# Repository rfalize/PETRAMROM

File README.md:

# PETRAMROM
PET RAM/ROM Replacement

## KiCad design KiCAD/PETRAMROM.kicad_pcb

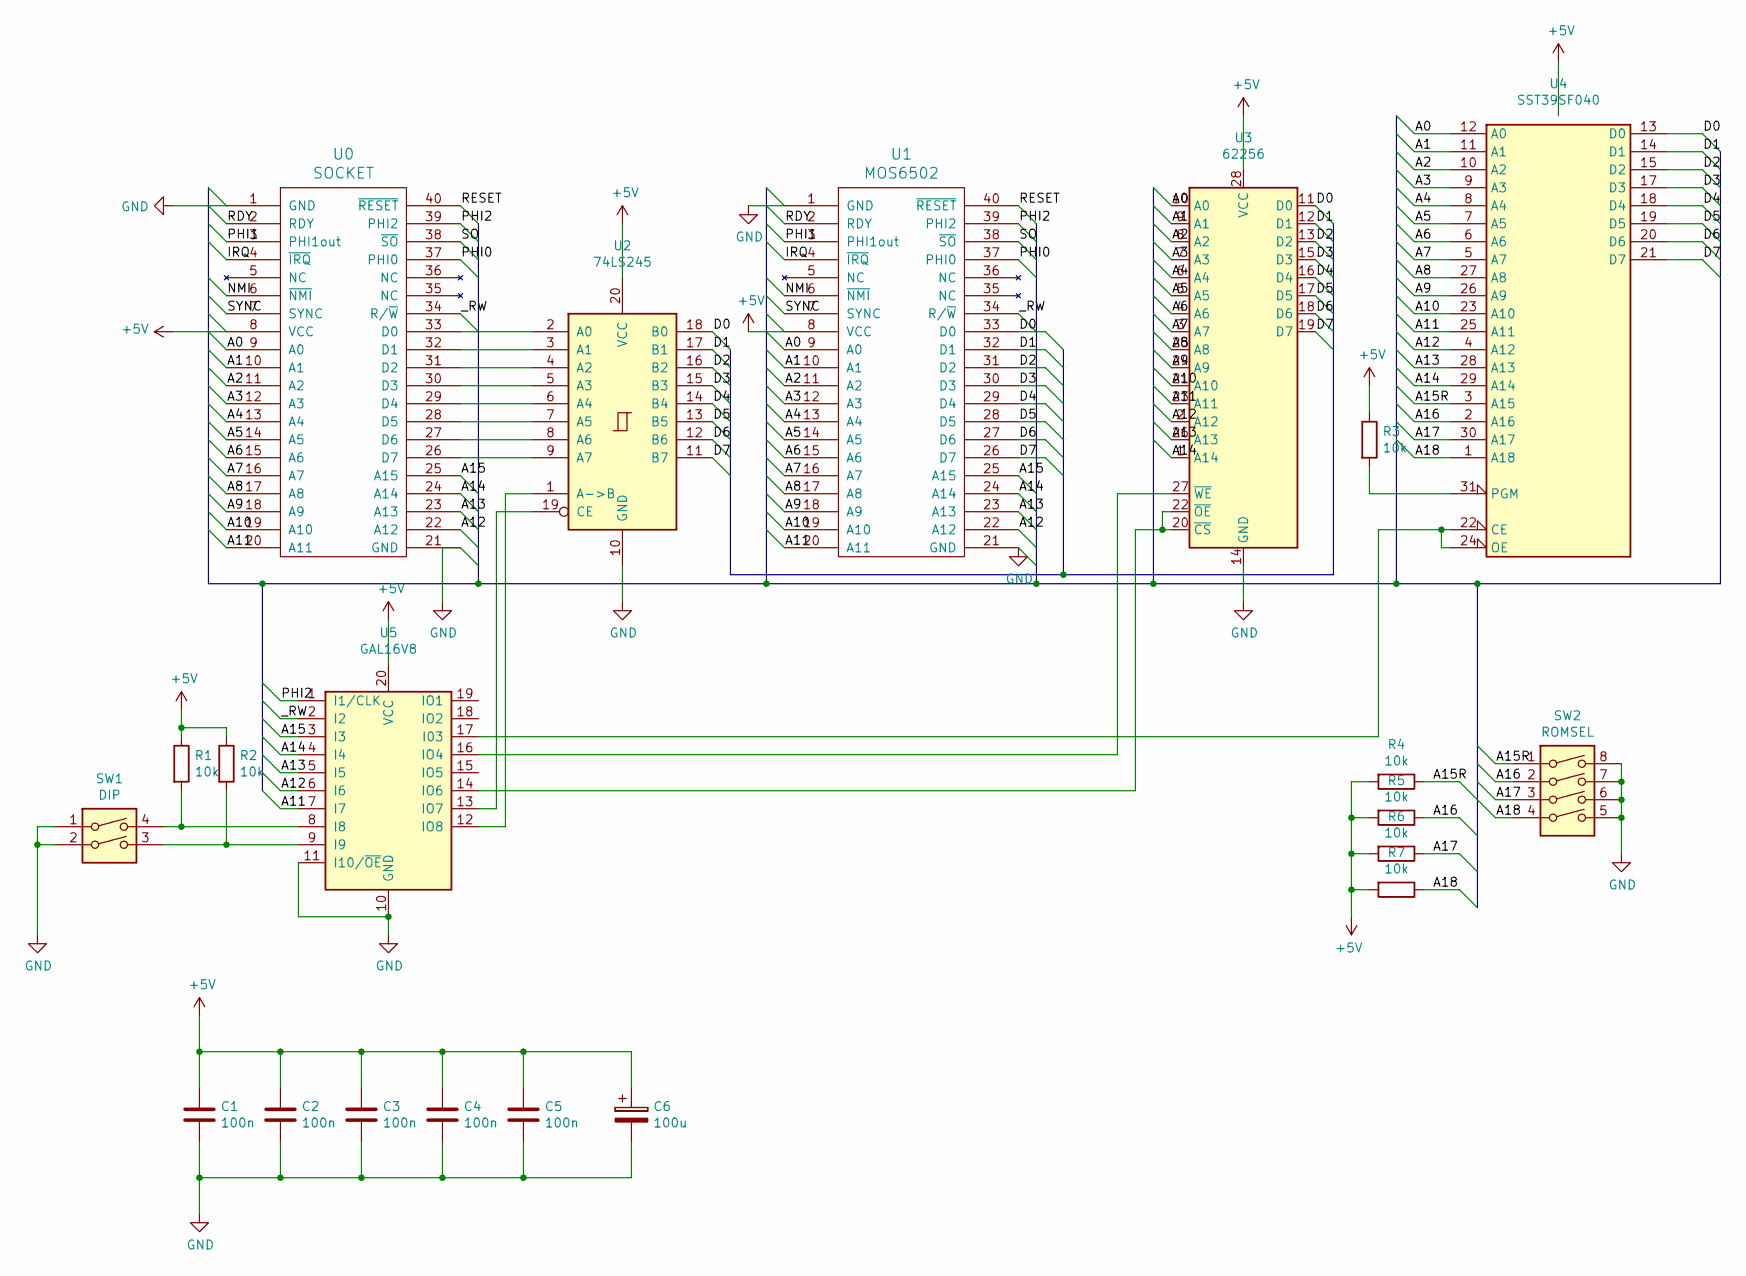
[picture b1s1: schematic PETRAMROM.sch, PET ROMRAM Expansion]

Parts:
C1, C2, C3, C4, C5: 100n; C_Disc_D5.0mm_W2.5mm_P5.00mm
C6: 100u; C_Radial_D6.3mm_H5.0mm_P2.50mm
R1, R2, R3, R4, R5, R6, R7: 10k; R_Axial_DIN0207_L6.3mm_D2.5mm_P2.54mm_Vertical
SW1: DIP; SW_DIP_SPSTx02_Slide_9.78x7.26mm_W7.62mm_P2.54mm
SW2: ROMSEL; SW_DIP_SPSTx04_Slide_9.78x12.34mm_W7.62mm_P2.54mm
U0: SOCKET; DIP-40_W15.24mm_Socket_LongPads
U1: MOS6502; DIP-40_W15.24mm_LongPads
U2: 74LS245; DIP-20_W7.62mm_LongPads
U3: 62256; DIP-28_W15.24mm_LongPads
U4: SST39SF040; DIP-32_W15.24mm_LongPads
U5: GAL16V8; DIP-20_W7.62mm_LongPads

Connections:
+5V: C1.1, C2.1, C3.1, C4.1, C5.1, C6.1, R1.1, R2.1, R3.1, R4.2, R5.2, R6.2, R7.2, U0.8 (VCC), U1.8 (VCC), U2.20 (VCC), U3.28 (VCC), U4.32 (VCC), U5.20 (VCC)
/A0: U0.9 (A0), U1.9 (A0), U3.10 (A0), U4.12 (A0)
/A1: U0.10 (A1), U1.10 (A1), U3.9 (A1), U4.11 (A1)
/A2: U0.11 (A2), U1.11 (A2), U3.8 (A2), U4.10 (A2)
/A3: U0.12 (A3), U1.12 (A3), U3.7 (A3), U4.9 (A3)
/A4: U0.13 (A4), U1.13 (A4), U3.6 (A4), U4.8 (A4)
/A5: U0.14 (A5), U1.14 (A5), U3.5 (A5), U4.7 (A5)
/A6: U0.15 (A6), U1.15 (A6), U3.4 (A6), U4.6 (A6)
/A7: U0.16 (A7), U1.16 (A7), U3.3 (A7), U4.5 (A7)
/A8: U0.17 (A8), U1.17 (A8), U3.25 (A8), U4.27 (A8)
/A9: U0.18 (A9), U1.18 (A9), U3.24 (A9), U4.26 (A9)
/A10: U0.19 (A10), U1.19 (A10), U3.21 (A10), U4.23 (A10)
/A11: U0.20 (A11), U1.20 (A11), U3.23 (A11), U4.25 (A11), U5.7 (I7)
/A12: U0.22 (A12), U1.22 (A12), U3.2 (A12), U4.4 (A12), U5.6 (I6)
/A13: U0.23 (A13), U1.23 (A13), U3.26 (A13), U4.28 (A13), U5.5 (I5)
/A14: U0.24 (A14), U1.24 (A14), U3.1 (A14), U4.29 (A14), U5.4 (I4)
/A15: U0.25 (A15), U1.25 (A15), U5.3 (I3)
/A15R: R4.1, SW2.1, U4.3 (A15)
/A16: R5.1, SW2.2, U4.2 (A16)
/A17: R6.1, SW2.3, U4.30 (A17)
/A18: R7.1, SW2.4, U4.1 (A18)
/D0: U1.33 (D0), U2.18 (B0), U3.11 (D0), U4.13 (D0)
/D1: U1.32 (D1), U2.17 (B1), U3.12 (D1), U4.14 (D1)
/D2: U1.31 (D2), U2.16 (B2), U3.13 (D2), U4.15 (D2)
/D3: U1.30 (D3), U2.15 (B3), U3.15 (D3), U4.17 (D3)
/D4: U1.29 (D4), U2.14 (B4), U3.16 (D4), U4.18 (D4)
/D5: U1.28 (D5), U2.13 (B5), U3.17 (D5), U4.19 (D5)
/D6: U1.27 (D6), U2.12 (B6), U3.18 (D6), U4.20 (D6)
/D7: U1.26 (D7), U2.11 (B7), U3.19 (D7), U4.21 (D7)
/IRQ: U0.4 (~IRQ), U1.4 (~IRQ)
/NMI: U0.6 (~NMI), U1.6 (~NMI)
/PHI0: U0.37 (PHI0), U1.37 (PHI0)
/PHI1: U0.3 (PHI1out), U1.3 (PHI1out)
/PHI2: U0.39 (PHI2), U1.39 (PHI2), U5.1 (I1/CLK)
/RDY: U0.2 (RDY), U1.2 (RDY)
/RESET: U0.40 (~RESET), U1.40 (~RESET)
/SO: U0.38 (~SO), U1.38 (~SO)
/SYNC: U0.7 (SYNC), U1.7 (SYNC)
/_RW: U0.34 (R/~W), U1.34 (R/~W), U5.2 (I2)
GND: C1.2, C2.2, C3.2, C4.2, C5.2, C6.2, SW1.1, SW1.2, SW2.5, SW2.6, SW2.7, SW2.8, U0.1 (GND), U0.21 (GND), U1.1 (GND), U1.21 (GND), U2.10 (GND), U3.14 (GND), U4.16 (GND), U5.10 (GND), U5.11 (I10/~OE~)
unnamed: R1.2, SW1.4, U5.8 (I8)
unnamed: R2.2, SW1.3, U5.9 (I9)
unnamed: R3.2, U4.31 (PGM)
unnamed: U0.26 (D7), U2.9 (A7)
unnamed: U0.27 (D6), U2.8 (A6)
unnamed: U0.28 (D5), U2.7 (A5)
unnamed: U0.29 (D4), U2.6 (A4)
unnamed: U0.30 (D3), U2.5 (A3)
unnamed: U0.31 (D2), U2.4 (A2)
unnamed: U0.32 (D1), U2.3 (A1)
unnamed: U0.33 (D0), U2.2 (A0)
unnamed: U2.1 (A->B), U5.12 (IO8)
unnamed: U2.19 (CE), U5.13 (IO7)
unnamed: U3.20 (~CS), U3.22 (~OE), U5.14 (IO6)
unnamed: U3.27 (~WE), U5.16 (IO4)
unnamed: U4.22 (CE), U4.24 (OE), U5.17 (I03)

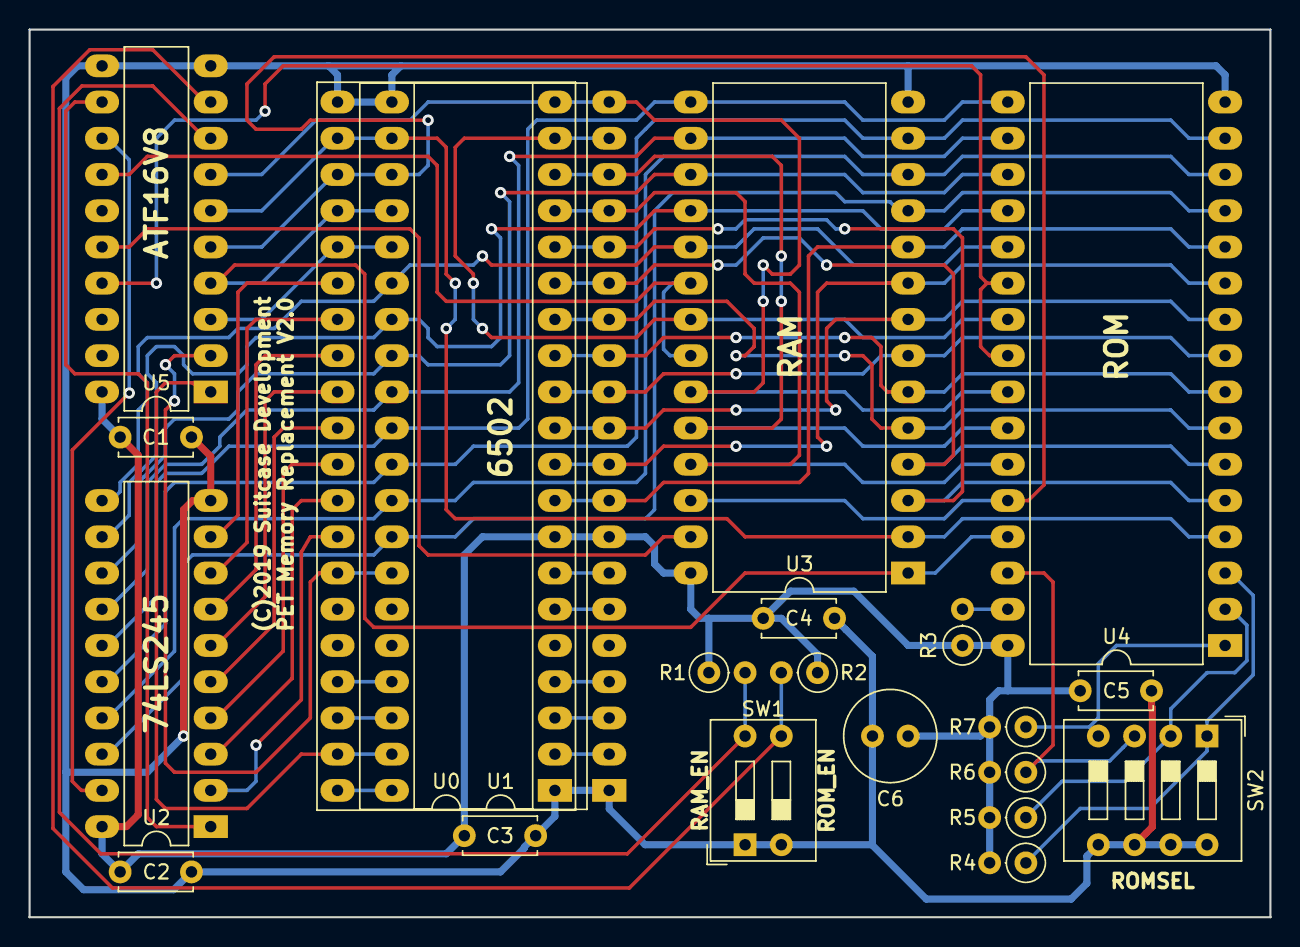
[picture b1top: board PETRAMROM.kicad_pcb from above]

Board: 2 copper layers, 87.0 x 62.2 mm, 21 parts (0 on the bottom side), 56 nets.

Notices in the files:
KiCAD/PETRAMROM.kicad_pcb:
(C)2019 Suitcase Development
